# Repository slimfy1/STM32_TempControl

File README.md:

This is STM32 PWM Controller. It's controll throught USB or USART pins. For example, you can use it for controll Raspberry Pi fans with PWM

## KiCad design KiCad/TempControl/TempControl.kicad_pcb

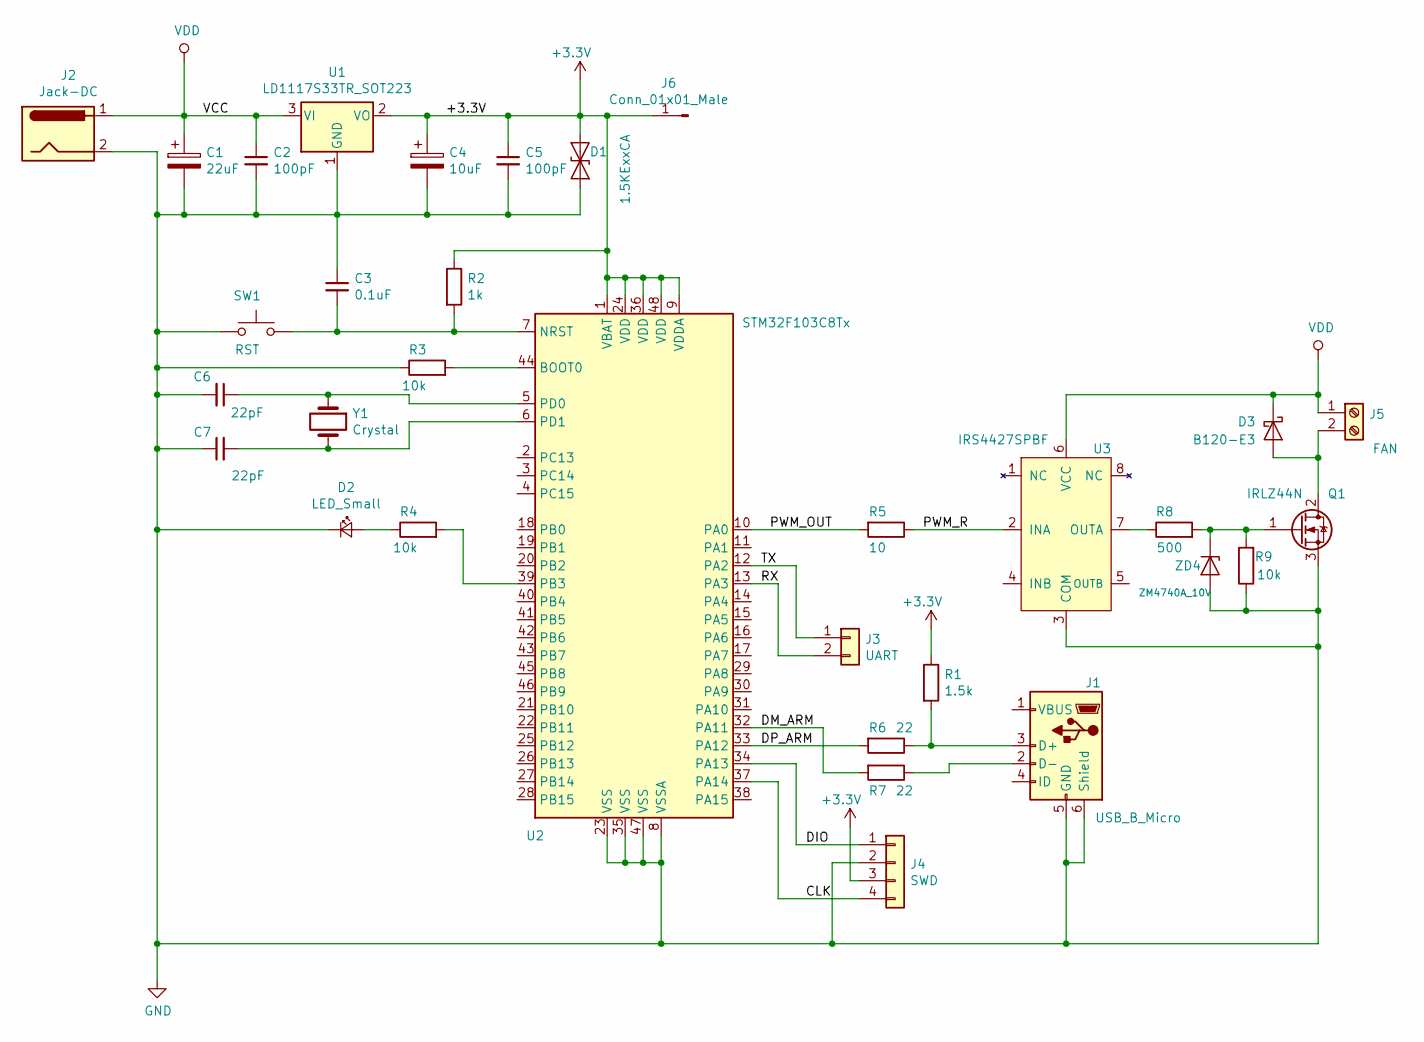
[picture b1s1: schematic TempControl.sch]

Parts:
C1: 22uF; CP_EIA-2012-12_Kemet-R
C2, C5: 100pF; C_0805_2012Metric
C3: 0.1uF; C_0805_2012Metric
C4: 10uF; CP_EIA-2012-12_Kemet-R
C6, C7: 22pF; C_0805_2012Metric
D1: 1.5KExxCA; D_SMB
D2: LED_Small; LED_0805_2012Metric
D3: B120-E3; D_SMB
J1: USB_B_Micro; USB_Mini-B_Lumberg_2486_01_Horizontal
J2: Jack-DC; BarrelJack_Wuerth_6941xx301002
J3: UART; PinHeader_1x02_P2.54mm_Vertical
J4: SWD; PinHeader_1x04_P2.54mm_Vertical
J5: FAN; TerminalBlock_bornier-2_P5.08mm
J6: Conn_01x01_Male; TestPoint_Pad_D2.0mm
Q1: IRLZ44N; TO-252-2_TabPin1
R1: 1.5k; R_0805_2012Metric
R2: 1k; R_0805_2012Metric
R3, R4, R9: 10k; R_0805_2012Metric
R5: 10; R_0805_2012Metric
R6, R7: 22; R_0805_2012Metric
R8: 500; R_0805_2012Metric
SW1: RST; SW_DIP_SPSTx01_Slide_6.7x4.1mm_W8.61mm_P2.54mm_LowProfile
U1: LD1117S33TR_SOT223; TO-252-2_TabPin1
U2: STM32F103C8Tx; LQFP-48_7x7mm_P0.5mm
U3: IRS4427SPBF; SOIC127P600X175-8N
Y1: Crystal; Crystal_SMD_HC49-SD
ZD4: ZM4740A_10V; D_MELF

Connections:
+3V3: C4.1, C5.1, D1.1 (A1), J4.3, J6.1, R1.1, R2.1, U1.2 (VO), U2.1 (VBAT), U2.9 (VDDA), U2.24 (VDD), U2.36 (VDD), U2.48 (VDD)
/CLK: J4.4, U2.37 (PA14)
/DIO: J4.1, U2.34 (PA13)
/DM_ARM: R7.2, U2.32 (PA11)
/DP_ARM: R6.2, U2.33 (PA12)
/PWM_OUT: R5.2, U2.10 (PA0)
/PWM_R: R5.1, U3.2 (INA)
/RX: J3.2, U2.13 (PA3)
/TX: J3.1, U2.12 (PA2)
GND: C1.2, C2.2, C3.1, C4.2, C5.2, C6.2, C7.1, D1.2 (A2), D2.1 (K), J1.5 (GND), J1.6 (Shield), J2.2, J2.3, J4.2, Q1.3 (S), R3.1, R9.1, SW1.1, U1.1 (GND), U2.8 (VSSA), U2.23 (VSS), U2.35 (VSS), U2.47 (VSS), U3.3 (COM), ZD4.2 (A); also elsewhere on the board
unnamed: C3.2, R2.2, SW1.2, U2.7 (NRST)
unnamed: C6.1, U2.5 (PD0), Y1.1
unnamed: C7.2, U2.6 (PD1), Y1.2
unnamed: D2.2 (A), R4.1
unnamed 14: D3.2 (A), J5.2, Q1.2 (D); also elsewhere on the board
unnamed: J1.2 (D-), R7.1
unnamed: J1.3 (D+), R1.2, R6.1
unnamed: Q1.1 (G), R8.2, R9.2, ZD4.1 (K)
unnamed: R3.2, U2.44 (BOOT0)
unnamed: R4.2, U2.39 (PB3)
unnamed: R8.1, U3.7 (OUTA)
VDD: C1.1, C2.1, D3.1 (K), J2.1, J5.1, U1.3 (VI), U3.6 (VCC)

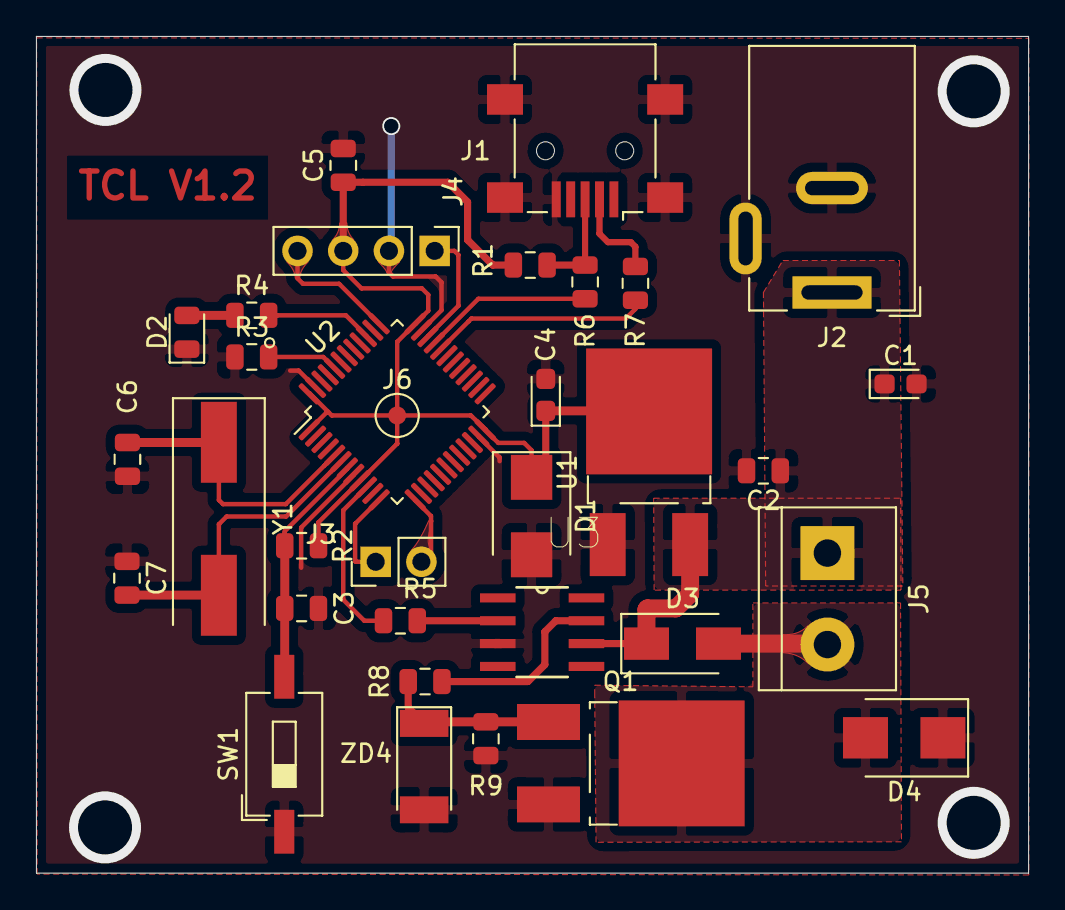
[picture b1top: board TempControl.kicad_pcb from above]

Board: 2 copper layers, 55.1 x 46.5 mm, 33 parts (0 on the bottom side), 22 nets.

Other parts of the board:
D4: 1.5KExxCA; D_SMB

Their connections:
GND: D4.1; also elsewhere on the board
unnamed 14: D4.2; also elsewhere on the board

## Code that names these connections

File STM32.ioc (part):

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Mcu.Name=STM32F103C(8-B)Tx
Mcu.Package=LQFP48
Mcu.UserName=STM32F103C8Tx
PA0-WKUP.GPIOParameters=GPIO_Speed
PA0-WKUP.GPIO_Speed=GPIO_SPEED_FREQ_HIGH
PA0-WKUP.Signal=S_TIM2_CH1_ETR
PA11.Mode=Device
PA11.Signal=USB_DM
PA12.Mode=Device
PA12.Signal=USB_DP
PA13.Mode=Serial_Wire
PA13.Signal=SYS_JTMS-SWDIO
PA14.Mode=Serial_Wire
PA14.Signal=SYS_JTCK-SWCLK
PB3.GPIOParameters=GPIO_Label
PB3.GPIO_Label=LED_PIN
PB3.Signal=GPIO_Output
PD0-OSC_IN.Mode=HSE-External-Oscillator
PD0-OSC_IN.Signal=RCC_OSC_IN
PD1-OSC_OUT.Mode=HSE-External-Oscillator
PD1-OSC_OUT.Signal=RCC_OSC_OUT
RCC.SYSCLKFreq_VALUE=48000000
RCC.SYSCLKSource=RCC_SYSCLKSOURCE_PLLCLK
board=custom

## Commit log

2020-03-13 Init Release
2020-03-13 Create LICENSE
2020-03-14 Add USB LED State
    Fix USB and USART1 conflict, Add USB led connect status
2020-03-30 New firmware for PCB V1.2
    Remaping pins for LED. HAL->CMSIS some change
2020-06-03 Add structure schematic
2020-06-03 Fix PCB
2020-10-07 Add RPI scripts
    Add RPI scripts
